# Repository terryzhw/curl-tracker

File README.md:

# Curl Tracker: Wearable Bicep Curl Coach

## What is Curl Tracker?

Curl Tracker is a wearable bicep curl tracker that uses an ESP32-C3 Super Mini alongside a MPU-6500 IMU to count reps, measure curl speed, and evaluate form in real-time. It uses a on-device classifier to distinguish good reps from common curl form faults. Curl Tracker displays live rep metrics to a SSD1306 OLED and streams data over MQTT to be plotted on a Python/matplotlib client. It also provides haptic feedback and monitoring of device state.

## Bicep-Curl Classifier
### Training:

### Collecting:

## Breadboard Prototype

### Design Choices:

- Power: 3.7V LiPo (range: 3.0V - 4.2V) with a TP4056 module for charging managment. MT3608 module converts the varying 3.7V Lipo to a stable 5V source. A mechanical switch is used as a on/off switch. 

- MCU & Peripherals: ESP32-C3 Super Mini is the MCU that serves as the brain for the project. MPU-6500 IMU and SSD1306 share a I2C bus which the ESP32 uses to communicate. A push button is used to provide data collection input to label reps while gathering training data for the classifier.

- Feedback: A status LED exists which turns on if any of the electronic malfunction. The OLED displays rep count, sets, and status of MQTT. The vibration motor, paired with a flyback diode circuit for back-EMF protection, is used for haptic feedback.

## KiCad Schematic & PCB layout 

### Design Choices: 

- ESP32-C3-MINI-1 module: Using a pre-certified module means the RF design is already done and the FCC/CE certification carries over, so I avoid the antenna layout, matching network, and re-testing that a bare C3 would require.
  
- MPU6500 → BMI270: The MPU6500 is end-of-life and no longer recommended for new designs. The BMI270 is Bosch's current-generation IMU with active vendor support and drivers in most major frameworks.
  
- TP4056 → MCP73831: Swapped the TP4056 for Microchip's MCP73831. Better documented, properly sourced through mainstream distributors, and easier to justify in a design review.
  
- MT3608 → TPS63001: A LiPo swings from 4.2 V down to 3.0 V, which straddles the 3.3 V rail from both directions. A boost-only converter or an LDO can't hold regulation across that whole range, so the TPS63001 buck-boost keeps 3.3 V stable through the full discharge curve, including the current spikes when the ESP32's radio transmits.
  
- USB-C: The current connector standard: reversible, mechanically more durable than micro-B, and what any user will already have a cable for.
  
- JST-PH for battery and motor: Keyed housings so the connectors can't be seated backwards, and they're cheap, common, and rated well past the current this board draws.

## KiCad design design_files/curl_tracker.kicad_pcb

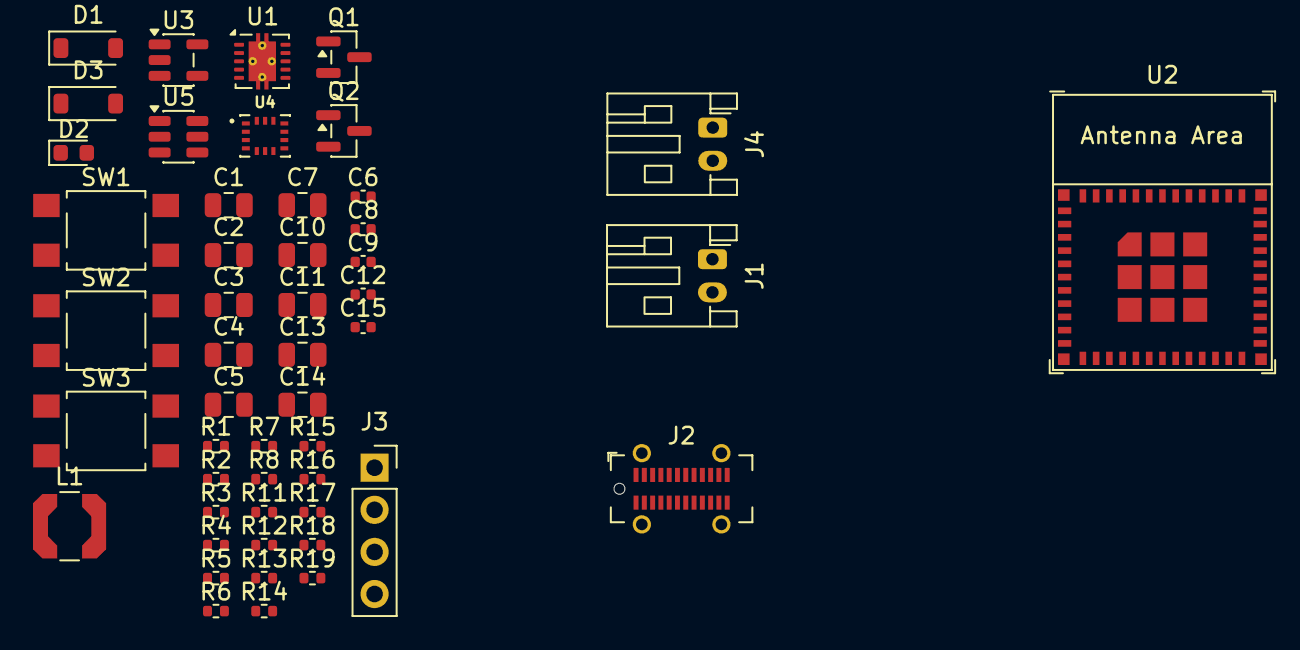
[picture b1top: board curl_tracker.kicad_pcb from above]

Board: 2 copper layers, 50 parts (0 on the bottom side), 29 nets, no tracks yet.

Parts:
C1, C2, C3, C4, C7: 10uF; C_0805_2012Metric
C5: 1uF; C_0805_2012Metric
C6, C8, C9, C12, C15: 100nF; C_0402_1005Metric
C10, C11: 4.7uF; C_0805_2012Metric
C13, C14: 100nF; C_0805_2012Metric
D1: MBR120; D_SOD-123
D2: LED; LED_0603_1608Metric
D3: 1N5819; D_SOD-123
J1, J4: JST-PH; JST_PH_S2B-PH-K_1x02_P2.00mm_Horizontal
J2: USB_C_Receptacle; USB_C_Receptacle_GCT_USB4115-03-C
J3: SSD1306 OLED; PinSocket_1x04_P2.54mm_Vertical
L1: 2.2uH; L_Coilcraft_LPS4018
Q1: DMP2035; SOT-23
Q2: AO3400A; SOT-23
R1, R4, R5: 100k; R_0402_1005Metric
R2, R18: 100; R_0402_1005Metric
R3, R6, R11, R12, R17, R19: 10k; R_0402_1005Metric
R7, R8: 4.7k; R_0402_1005Metric
R13, R14: 5.1k; R_0402_1005Metric
R15: 470; R_0402_1005Metric
R16: 5k; R_0402_1005Metric
SW1, SW2, SW3: SW_Push; SW_SPST_TL3305A
U1: TPS63001; Texas_DRC0010J_ThermalVias
U2: ESP32-C3-MINI-1
U3: MCP73831-2-OT; SOT-23-5
U4: BMI270; XDCR_BMI270
U5: USBLC6-2SC6; SOT-23-6

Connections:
+3.3V: C3.2, C4.2, C7.1, C8.1, C12.2, C13.1, C14.1, C15.1, D3.1 (K), J3.2, J4.1, R3.1, R6.1, R7.1, R8.1, R11.2, R12.2, R17.1, U1.1 (VOUT), U1.10 (FB), U2.3 (3V3), U4.2 (ASDX), U4.3 (ASCX), U4.5 (VDDIO), U4.8 (VDD), U4.12 (CSB)
+5V: C9.2, C10.1, D1.2 (A), D2.2 (A), J2.A4 (VBUS), J2.A9 (VBUS), J2.B4 (VBUS), J2.B9 (VBUS), Q1.2 (G), R1.1, U3.4 (V_{DD}), U5.5 (VBUS)
/IO3: U2.6 (GPIO3/ADC1_CH3), U4.4 (INT1)
/IO4: R18.1, U2.18 (GPIO4/ADC1_CH4)
/IO5: R17.2, SW3.2, U2.19 (GPIO5/ADC2_CH0)
/SCL: J3.3, R7.2, U2.20 (GPIO6), U4.13 (SCX)
/SDA: J3.4, R8.2, U2.21 (GPIO7), U4.14 (SDX)
/USB_N: U2.26 (GPIO18/USB_D-), U5.4 (I/O2)
/USB_P: U2.27 (GPIO19/USB_D+), U5.6 (I/O1)
GND: C1.1, C2.2, C3.1, C4.1, C5.2, C6.2, C7.2, C8.2, C9.1, C10.2, C11.2, C12.1, C13.2, C14.2, J1.2, J2.A1 (GND), J2.A12 (GND), J2.B1 (GND), J2.B12 (GND), J2.SH (SHIELD), J3.1, Q2.2 (S), R1.2, R5.2, R13.2, R14.2, R16.1, R19.1, SW1.1, SW2.2, SW3.1, U1.3 (PGND), U1.7 (PS/SYNC), U1.9 (GND), U1.11 (PGND), U2.1 (GND), U2.2 (GND), U2.11 (GND), U2.14 (GND), U2.36 (GND), U2.37 (GND), U2.38 (GND), U2.39 (GND), U2.40 (GND), U2.41 (GND), U2.42 (GND), U2.43 (GND), U2.44 (GND), U2.45 (GND), U2.46 (GND), U2.47 (GND), U2.48 (GND), U2.49 (GND), U2.50 (GND), U2.51 (GND), U2.52 (GND), U2.53 (GND), U3.2 (V_{SS}), U4.1 (SDO), U4.6 (GNDIO), U4.7 (GND), U5.2 (GND)
unnamed: C1.2, D1.1 (K), Q1.3 (S), R2.1, U1.5 (VIN)
unnamed: D2.1 (K), R15.2
unnamed: C15.2, D3.2 (A), J4.2, Q2.3 (D)
unnamed: J2.A5 (CC1), R13.1
unnamed: J2.B5 (CC2), R14.1
unnamed: J2.A6 (D+), J2.B6 (D+), U5.3 (I/O2)
unnamed: J2.A7 (D-), J2.B7 (D-), U5.1 (I/O1)
unnamed: Q2.1 (G), R18.2, R19.2
unnamed: C2.1, R2.2, U1.6 (EN), U1.8 (VINA)
unnamed: L1.2, U1.4 (L1)
unnamed: L1.1, U1.2 (L2)
unnamed: C5.1, R3.2, SW1.2, U2.8 (EN/CHIP_PU)
unnamed: C6.1, R4.2, R5.1, U2.12 (GPIO0/ADC1_CH0/XTAL_32K_P)
unnamed: R6.2, U2.5 (GPIO2/ADC1_CH2)
unnamed: R11.1, U2.22 (GPIO8)
unnamed: R12.1, SW2.1, U2.23 (GPIO9)
unnamed: R16.2, U3.5 (PROG)
unnamed: R15.1, U3.1 (STAT)
VBATT: C11.1, J1.1, Q1.1 (D), R4.1, U3.3 (V_{BAT})

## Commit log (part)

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2026-05-01 Add images to README
    Add images to the README file.
2026-05-01 better readme
2026-05-01 Refine README content for clarity and accuracy
    Updated the README to clarify input descriptions and current prototype details.
2026-05-21 Revise README with project updates and roadmap
    Updated project description, added current build details, and outlined roadmap for future work.
2026-05-26 Revise README with new build images and sections
    Updated images and sections for past and current builds in README.
2026-05-26 Expand README with project description and schematic
    Added project overview and initial schematic details.
2026-05-26 Revise README for current build and usage updates
    Updated the README to reflect changes in the project's current build and installation instructions.
2026-05-26 Fix typo in Curl Tracker description
2026-05-26 Add Arduino code for MPU6050 and OLED display
2026-05-27 Enhance motion detection and feedback mechanisms
    Refactor angle calculations and add rep/set detection.
2026-05-28 Fix formatting issues in README.md
2026-05-28 Update README with future project plans
    Added future plans for MQTT implementation and enclosure design.
2026-05-28 Update README with plans and clean up formatting
    Removed extra line breaks and added plans for future implementation.
2026-06-02 Replace hardware schematic image URL
    Updated hardware schematic image in README.md.
2026-06-02 Update hardware schematic and description in README
    Updated hardware schematic image and added description for the initial schematic.
2026-06-02 Update hardware schematic and add design notes
    Updated hardware schematic image and added notes about the design and prototype verification.
2026-06-02 Update hardware schematic and description in README
    Updated the hardware schematic image and corrected the description of the schematic.
2026-06-02 Revise Curl Tracker schematic description
    Updated the description of the Curl Tracker schematic to include a flyback protection circuit and a voltage regulator.
2026-06-06 Add State Machine section to README
    Added a section about the state machine for rep counting.
2026-06-06 fully realized state machine
2026-06-07 Update README with final prototype design information
    Added final prototype design details and images to README.
2026-06-07 Rearrange sections in README for clarity
2026-06-30 Update README to remove outdated sections
    Removed sections on State Machine, Hardware Schematic, and Plans from the README.
